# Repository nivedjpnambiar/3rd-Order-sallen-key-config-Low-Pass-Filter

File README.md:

# 3rd-Order-sallen-key-config-Low-Pass-Filter
The filtering stage takes the mixed output of the lock-in amplifier and suppresses the remaining AC content so that the signal becomes as close as possible to a DC level. That DC-like output can then be used as a stable measurement value instead of a rapidly oscillating waveform.

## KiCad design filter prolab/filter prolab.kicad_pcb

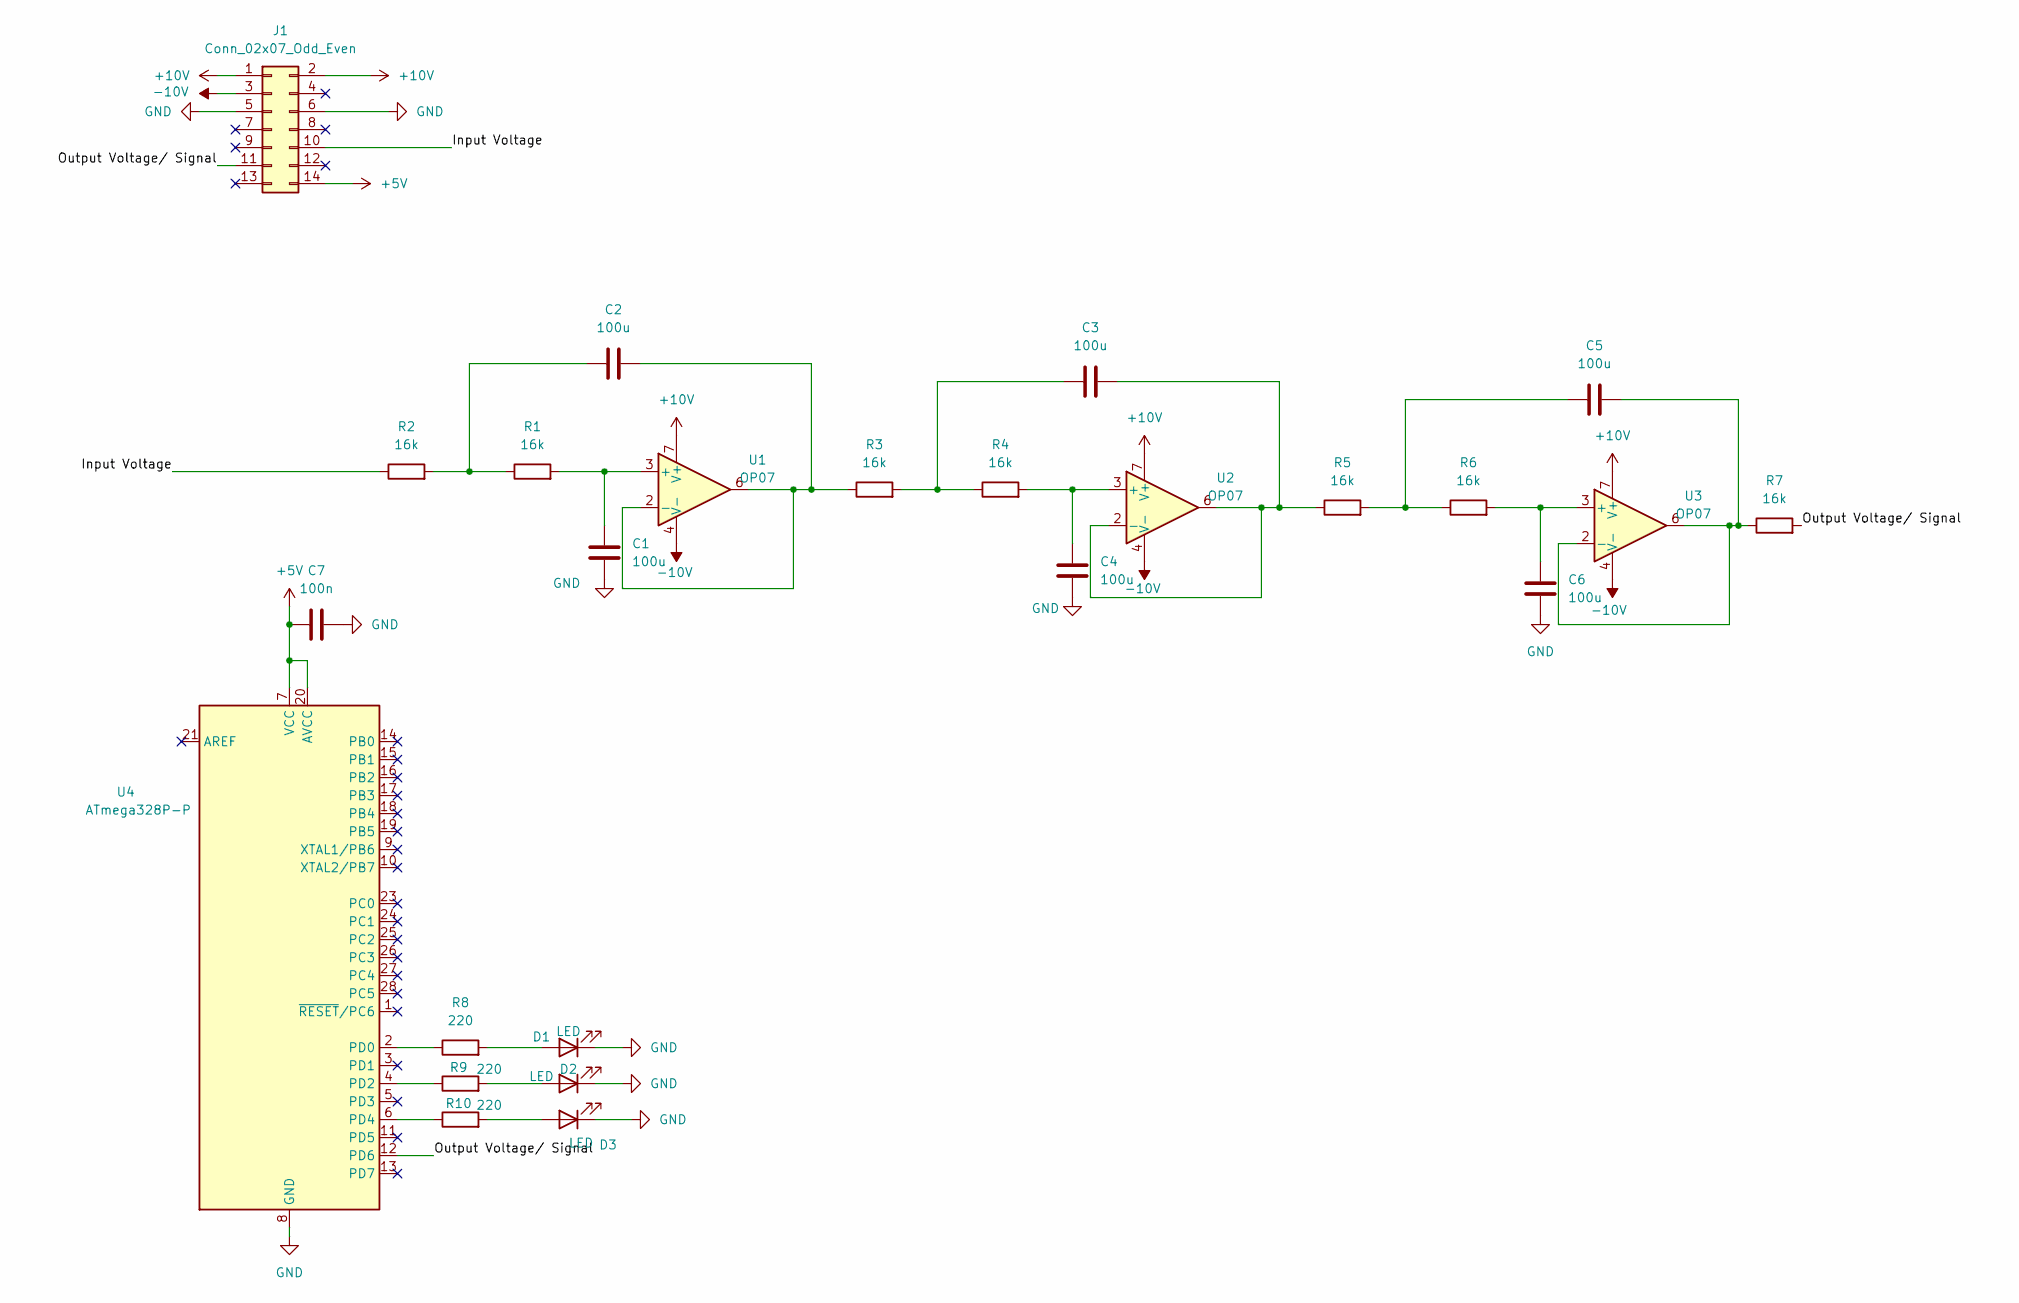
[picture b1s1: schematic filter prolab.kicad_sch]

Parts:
C1, C2, C3, C4, C5, C6: 100u; C_Disc_D5.0mm_W2.5mm_P5.00mm
C7: 100n; C_Disc_D5.0mm_W2.5mm_P5.00mm
D1, D2, D3: LED; LED_D3.0mm
J1: Conn_02x07_Odd_Even; Busstecker
R1, R2, R3, R4, R5, R6, R7: 16k; R_Axial_DIN0207_L6.3mm_D2.5mm_P10.16mm_Horizontal
R8, R9, R10: 220; R_Axial_DIN0207_L6.3mm_D2.5mm_P10.16mm_Horizontal
U1, U2, U3: OP07; DIP-8_W7.62mm_Socket_LongPads
U4: ATmega328P-P; DIP-28_W7.62mm_LongPads

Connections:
+5V: C7.2, J1.14, U4.7 (VCC), U4.20 (AVCC)
+10V: J1.1, J1.2, U1.7 (V+), U2.7 (V+), U3.7 (V+)
-10V: J1.3, U1.4 (V-), U2.4 (V-), U3.4 (V-)
/Input Voltage: J1.10, R2.1
/Output Voltage/ Signal: J1.11, R7.2, U4.12 (PD6)
GND: C1.2, C4.2, C6.2, C7.1, D1.1 (K), D2.1 (K), D3.1 (K), J1.5, J1.6, U4.8 (GND), U4.22 (GND)
unnamed: C2.1, R1.1, R2.2
unnamed: C3.1, R3.2, R4.1
unnamed: C5.1, R5.2, R6.1
unnamed: D1.2 (A), R8.2
unnamed: D2.2 (A), R9.2
unnamed: D3.2 (A), R10.2
unnamed: C1.1, R1.2, U1.3 (+)
unnamed: C2.2, R3.1, U1.2 (-), U1.6
unnamed: C4.1, R4.2, U2.3 (+)
unnamed: C3.2, R5.1, U2.2 (-), U2.6
unnamed: C6.1, R6.2, U3.3 (+)
unnamed: C5.2, R7.1, U3.2 (-), U3.6
unnamed: R8.1, U4.2 (PD0)
unnamed: R9.1, U4.4 (PD2)
unnamed: R10.1, U4.6 (PD4)

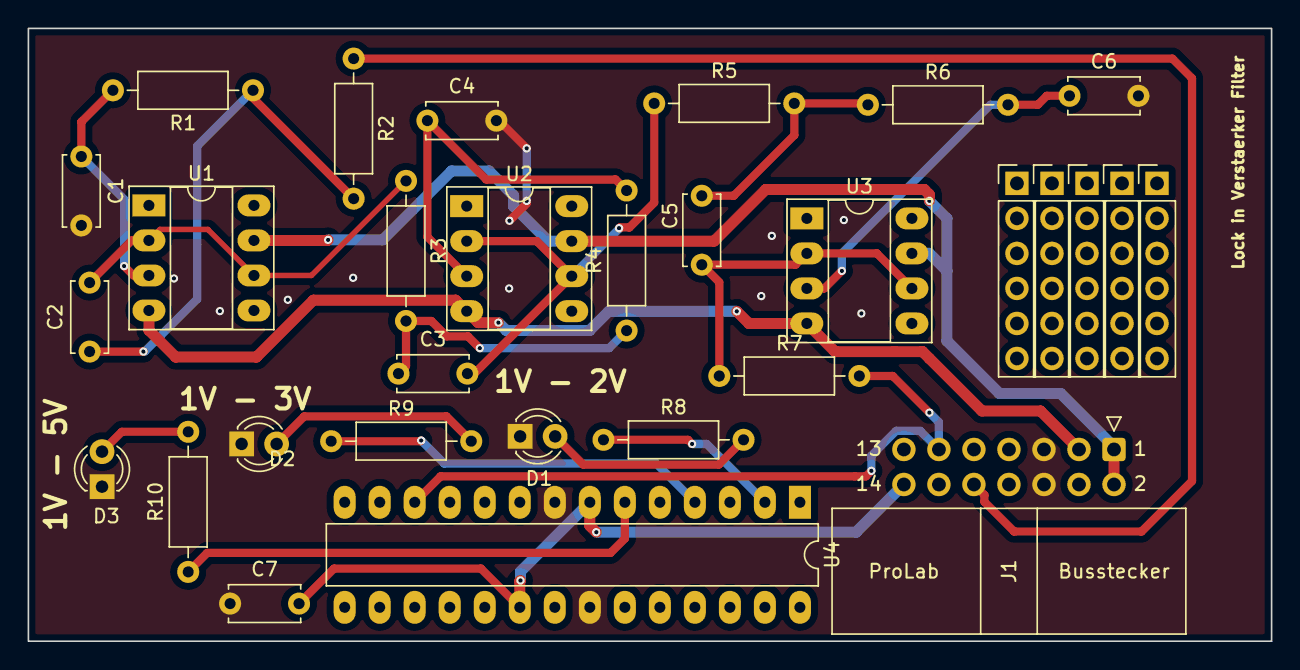
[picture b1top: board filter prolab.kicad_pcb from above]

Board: 2 copper layers, 90.2 x 44.5 mm, 25 parts (0 on the bottom side), 21 nets.

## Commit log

2026-03-25 Complete circuit files
    Download all of this to one folder, then open the KiCad project file and voila!
2026-03-25 Summary of Abschlussbericht
    Summary of what was done and how it was all measured!
